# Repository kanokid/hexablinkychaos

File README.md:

# HexaBlinkyChaos

HexaBlinkyChaos is a amped up blinky board featuring 3 CD4017 ICs, one for normal mode (it acts like your typical blinky) and 2 for chaos mode (which has one for all odd LEDs and one for all even LEDs. with reset pins for even more chaos!) It has 10 LEDs like normal, and uses the NE555P IC for clock timing. It also includes an optional USB-C port for your convenience.  (because why not) It uses 3 SPDT slide switches in total, 1 is to change between normal and chaos mode and the other 2 are for chaos mode, letting you run only evens or odds with one, or both with the last switch. I also have 2 of the CD4017 ICs (for chaos mode) set to count to 5 instead of 10. 1N4148 diodes are used to prevent backfeeding into the ICs since 2 ICs share 1 LED, but only is used at a time.

### Pictures:
Schematic:

PCB:

PCB Render:

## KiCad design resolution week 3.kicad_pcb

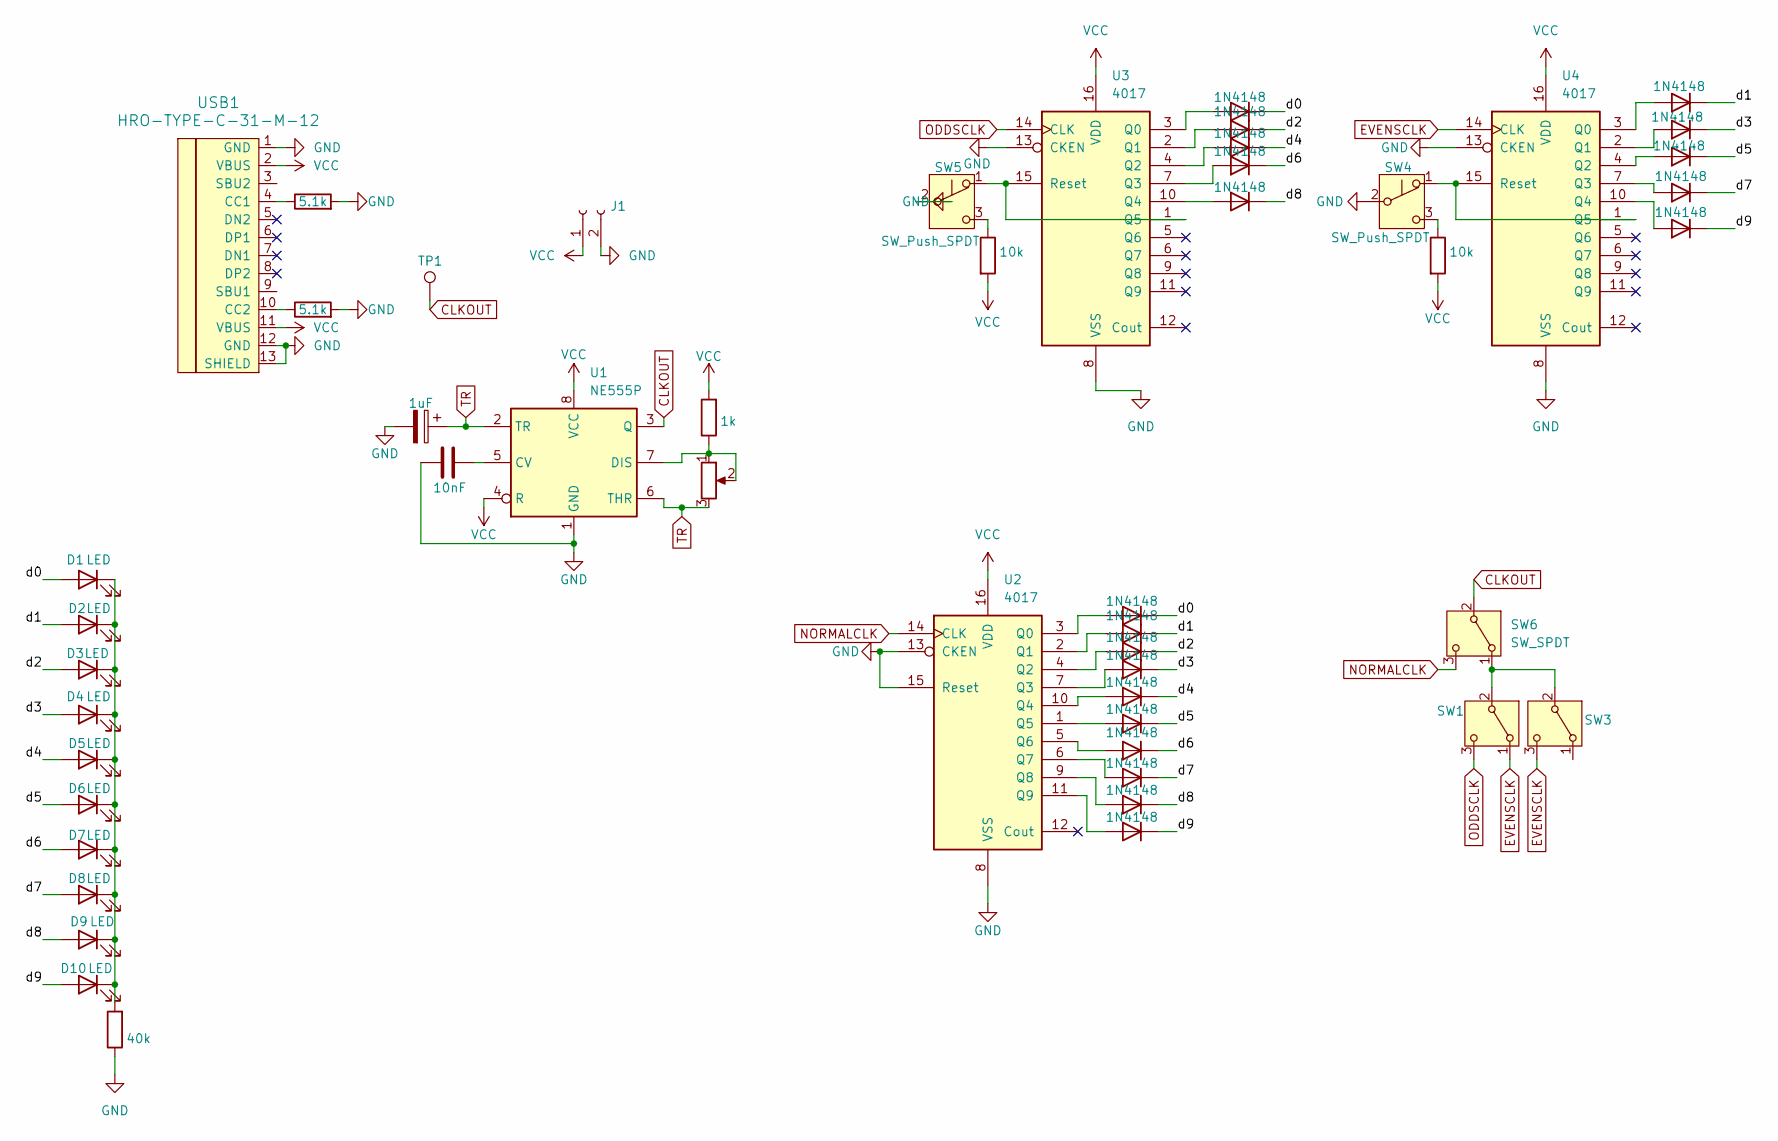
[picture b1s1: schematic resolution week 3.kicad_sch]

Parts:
C1: 1uF; CP_Radial_D5.0mm_P2.00mm
C2: 10nF; C_Disc_D7.5mm_W2.5mm_P5.00mm
D1, D2, D3, D4, D5, D6, D7, D8, D9, D10: LED; LED_D5.0mm
D11, D12, D13, D14, D15, D16, D17, D18, D19, D20, D21, D22, D23, D24, D25, D26, D27, D28, D29, D30: 1N4148; D_DO-35_SOD27_P7.62mm_Horizontal
J1: Conn_01x02_Socket; PinHeader_1x02_P2.54mm_Vertical
R1, R3: 10k; R_Axial_DIN0204_L3.6mm_D1.6mm_P7.62mm_Horizontal
R2: 1k; R_Axial_DIN0204_L3.6mm_D1.6mm_P7.62mm_Horizontal
R4: 40k; R_Axial_DIN0204_L3.6mm_D1.6mm_P7.62mm_Horizontal
R5, R6: 5.1k; R_Axial_DIN0204_L3.6mm_D1.6mm_P7.62mm_Horizontal
RV1: R_Potentiometer; Potentiometer_Vishay_T93YA_Vertical
SW1, SW3, SW6: SW_SPDT; SS12D10G5
SW4, SW5: SW_Push_SPDT; SW_XKB_DM1-16UC-1-edited
TP1: TestPoint; TestPoint_Pad_2.5x2.5mm
U1: NE555P; DIP-8_W7.62mm
U2, U3, U4: 4017; N16
USB1: HRO-TYPE-C-31-M-12

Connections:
/d0: D1.2 (A), D11.1 (K), D16.1 (K)
/d1: D2.2 (A), D12.1 (K), D22.1 (K)
/d2: D3.2 (A), D18.1 (K), D23.1 (K)
/d3: D4.2 (A), D13.1 (K), D24.1 (K)
/d4: D5.2 (A), D19.1 (K), D25.1 (K)
/d5: D6.2 (A), D17.1 (K), D26.1 (K)
/d6: D7.2 (A), D20.1 (K), D27.1 (K)
/d7: D8.2 (A), D14.1 (K), D28.1 (K)
/d8: D9.2 (A), D21.1 (K), D29.1 (K)
/d9: D10.2 (A), D15.1 (K), D30.1 (K)
CLKOUT: SW6.2 (B), TP1.1, U1.3 (Q)
EVENSCLK: SW1.1 (A), SW3.3 (C), U4.14 (CLK)
GND: C1.2, C2.1, J1.2, R4.1, R5.2, R6.2, SW4.2 (B), SW5.2 (B), U1.1 (GND), U2.8 (VSS), U2.13 (CKEN), U2.15 (Reset), U3.8 (VSS), U3.13 (CKEN), U4.8 (VSS), U4.13 (CKEN), USB1.1 (GND), USB1.12 (GND), USB1.13 (SHIELD)
NORMALCLK: SW6.3 (C), U2.14 (CLK)
unnamed: D1.1 (K), D2.1 (K), D3.1 (K), D4.1 (K), D5.1 (K), D6.1 (K), D7.1 (K), D8.1 (K), D9.1 (K), D10.1 (K), R4.2
unnamed: D11.2 (A), U2.3 (Q0)
unnamed: D12.2 (A), U4.3 (Q0)
unnamed: D13.2 (A), U4.2 (Q1)
unnamed: D14.2 (A), U4.7 (Q3)
unnamed: D15.2 (A), U4.10 (Q4)
unnamed: D16.2 (A), U3.3 (Q0)
unnamed: D17.2 (A), U4.4 (Q2)
unnamed: D18.2 (A), U3.2 (Q1)
unnamed: D19.2 (A), U3.4 (Q2)
unnamed: D20.2 (A), U3.7 (Q3)
unnamed: D21.2 (A), U3.10 (Q4)
unnamed: D22.2 (A), U2.2 (Q1)
unnamed: D23.2 (A), U2.4 (Q2)
unnamed: D24.2 (A), U2.7 (Q3)
unnamed: D25.2 (A), U2.10 (Q4)
unnamed: D26.2 (A), U2.1 (Q5)
unnamed: D27.2 (A), U2.5 (Q6)
unnamed: D28.2 (A), U2.6 (Q7)
unnamed: D29.2 (A), U2.9 (Q8)
unnamed: D30.2 (A), U2.11 (Q9)
unnamed: SW1.2 (B), SW3.2 (B), SW6.1 (A)
unnamed: SW4.1 (A), U4.1 (Q5), U4.15 (Reset)
unnamed: R1.1, SW4.3 (C)
unnamed: SW5.1 (A), U3.1 (Q5), U3.15 (Reset)
unnamed: R3.1, SW5.3 (C)
unnamed: C2.2, U1.5 (CV)
unnamed: R2.1, RV1.1, RV1.2, U1.7 (DIS)
unnamed: R6.1, USB1.4 (CC1)
unnamed: R5.1, USB1.10 (CC2)
ODDSCLK: SW1.3 (C), U3.14 (CLK)
TR: C1.1, RV1.3, U1.2 (TR), U1.6 (THR)
VCC: J1.1, R1.2, R2.2, R3.2, U1.4 (R), U1.8 (VCC), U2.16 (VDD), U3.16 (VDD), U4.16 (VDD), USB1.2 (VBUS), USB1.11 (VBUS)

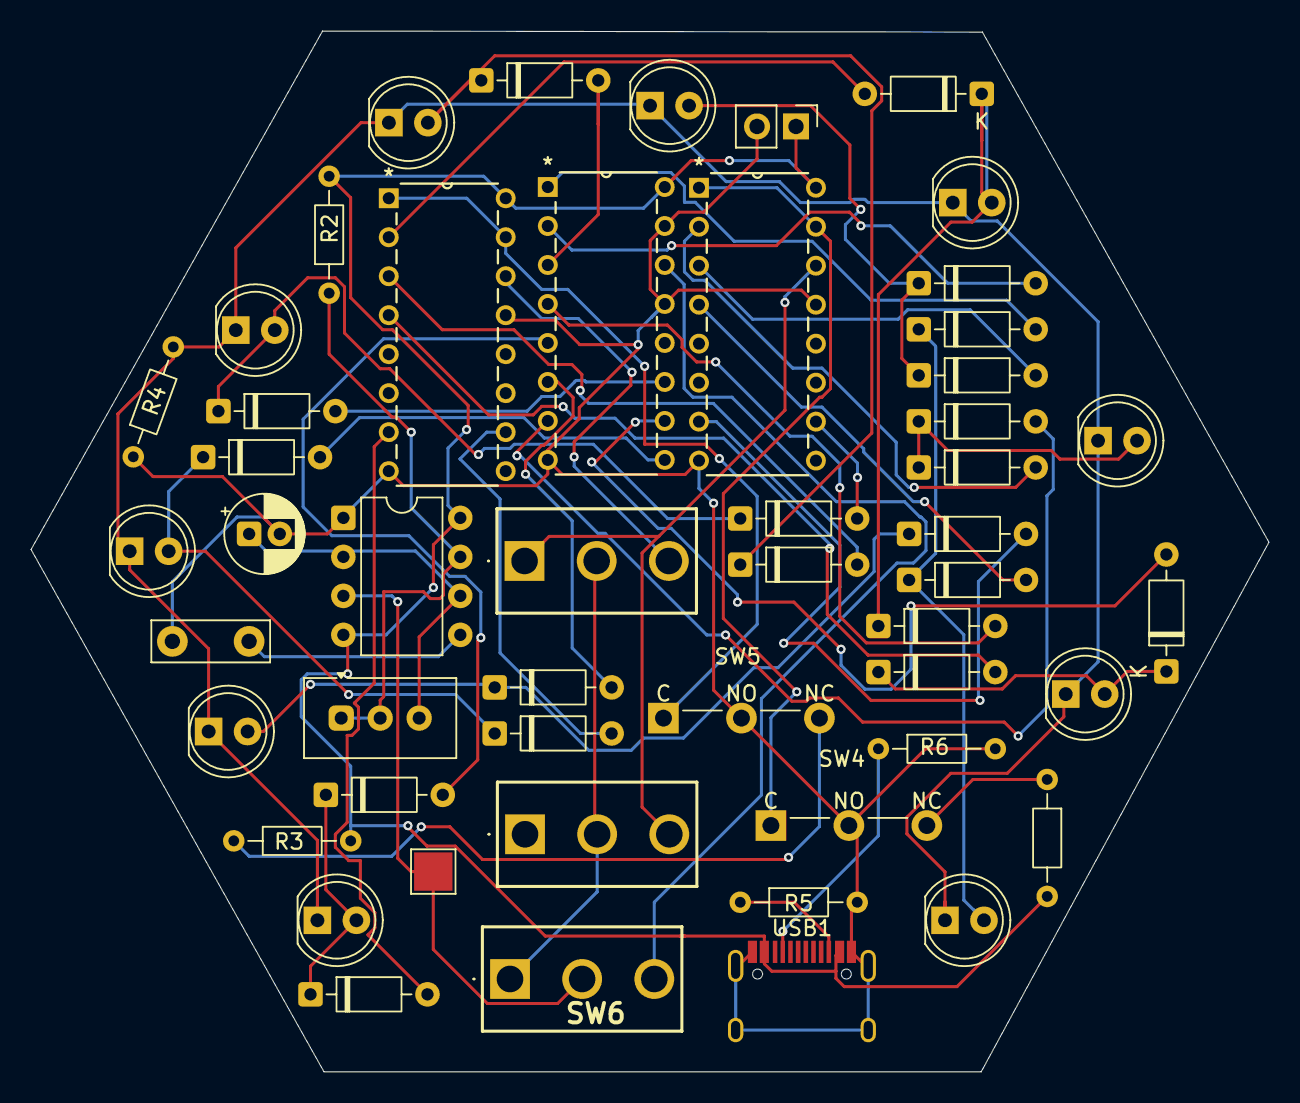
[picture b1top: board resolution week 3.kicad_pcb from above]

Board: 2 copper layers, 80.7 x 67.8 mm, 51 parts (0 on the bottom side), 47 nets.

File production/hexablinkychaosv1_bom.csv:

Designator,Footprint,Quantity,Value,LCSC Part #
C1,CP_Radial_D5.0mm_P2.00mm,1,1uF,
C2,C_Disc_D7.5mm_W2.5mm_P5.00mm,1,10nF,
"D1, D10, D2, D3, D4, D5, D6, D7, D8, D9",LED_D5.0mm,10,LED,
"D11, D12, D13, D14, D15, D16, D17, D18, D19, D20, D21, D22, D23, D24, D25, D26, D27, D28, D29, D30",D_DO-35_SOD27_P7.62mm_Horizontal,20,1N4148,
J1,PinHeader_1x02_P2.54mm_Vertical,1,Conn_01x02_Socket,
"R1, R3",R_Axial_DIN0204_L3.6mm_D1.6mm_P7.62mm_Horizontal,2,10k,
R2,R_Axial_DIN0204_L3.6mm_D1.6mm_P7.62mm_Horizontal,1,1k,
R4,R_Axial_DIN0204_L3.6mm_D1.6mm_P7.62mm_Horizontal,1,40k,
"R5, R6",R_Axial_DIN0204_L3.6mm_D1.6mm_P7.62mm_Horizontal,2,5.1k,
RV1,Potentiometer_Vishay_T93YA_Vertical,1,R_Potentiometer,
"SW1, SW3, SW6",SS12D10G5,3,SW_SPDT,
"SW4, SW5",SW_XKB_DM1-16UC-1-edited,2,SW_Push_SPDT,
TP1,TestPoint_Pad_2.5x2.5mm,1,TestPoint,
U1,DIP-8_W7.62mm,1,NE555P,
"U2, U3, U4",N16,3,4017,
USB1,HRO-TYPE-C-31-M-12,1,HRO-TYPE-C-31-M-12,

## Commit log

2026-04-17 removed some files and organized and mostly done with readme.
2026-04-17 Update README with schematic and PCB images
    Added schematic and PCB images to the README.
